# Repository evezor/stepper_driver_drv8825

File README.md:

# DRV8825 Stepper Motor Driver V1.0

*please note this board has been deprecated.

This board uses the Evezor Stamp STMF405 MCU

source: https://github.com/evezor/Evezor-Stamp-STMF405

An edge board with a DRV8825 stepper motor driver, limit switch connections and encoder inputs 

source files: https://github.com/evezor/v0_stepper_driver_drv8825

Evezor® and all associated marks, logos, and designs are registered trademarks and protected by copyright. Unauthorized use or reproduction of these trademarks and copyrighted materials is strictly prohibited.

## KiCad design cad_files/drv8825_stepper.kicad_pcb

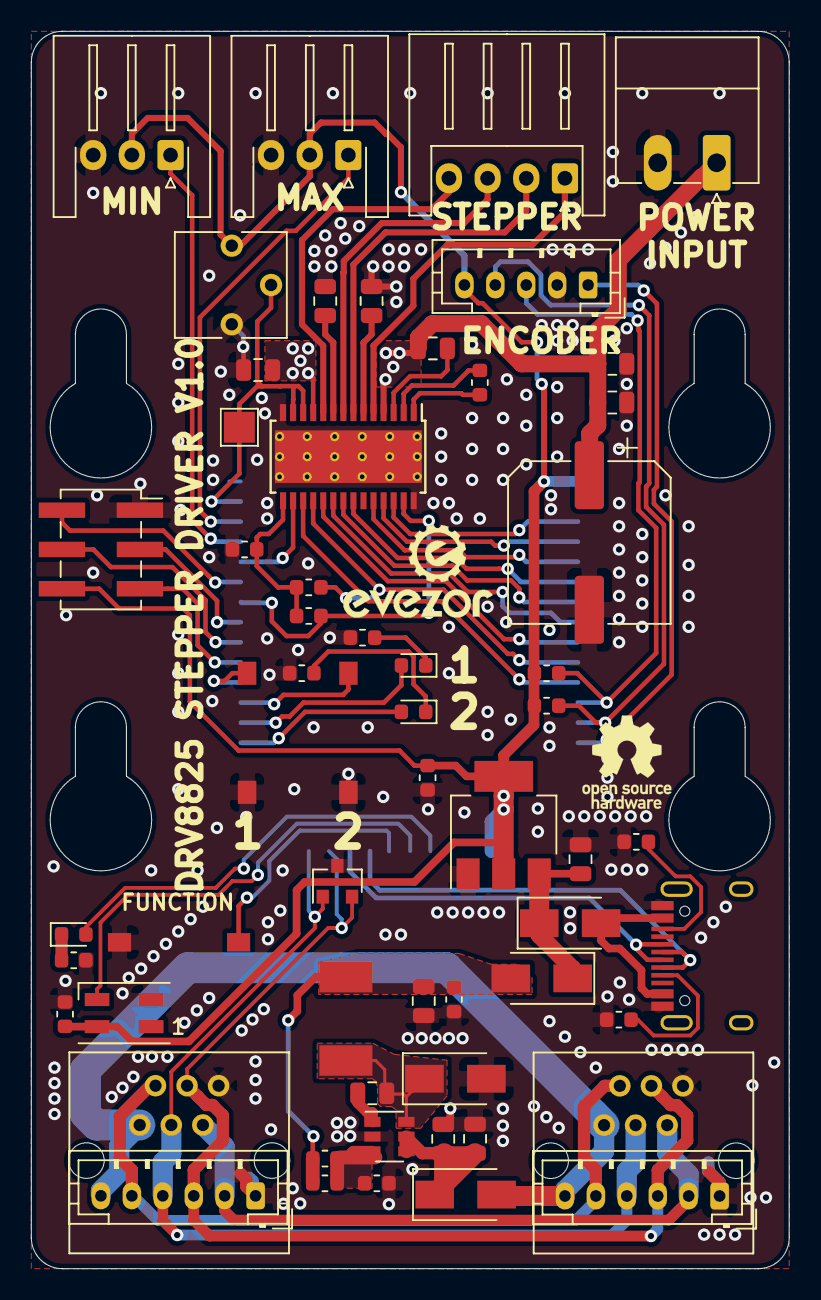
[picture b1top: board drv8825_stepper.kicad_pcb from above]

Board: 2 copper layers, 49.0 x 80.0 mm, 59 parts (1 on the bottom side), 60 nets.

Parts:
C1, C3, C12, C13, C15: .1uF 100V; C_0805_2012Metric
C2, C5, C9, C10: .1uF; C_0603_1608Metric
C4, C7: 4.7uF; C_0805_2012Metric
C6: 22uF; C_0805_2012Metric
C8: 10uF; C_0805_2012Metric
C11: 10 nF; C_0603_1608Metric
C14: 0.47uF; C_0603_1608Metric
C16: 100uF; CP_Elec_10x7.7
D1, D2, D4, D5: SX35_SCHOTTKY; D_SMA
D3, D8, D9: LED; LED_0603_1608Metric
D6: SK6812MINI; LED_SK6812MINI_PLCC4_3.5x3.5mm_P1.75mm
D7: D_TVS_x2_AAC; SOT-23
J1: USB_C_Receptacle_USB2.0; USB_C_Receptacle_HRO_TYPE-C-31-M-12
J2, J3: RJ11; RJ11_C189747_Horizontal
J4, J5: PH; JST_PH_B6B-PH-K_1x06_P2.00mm_Vertical
J6: Conn_02x03_Odd_Even; PinSocket_2x03_P2.54mm_Vertical_SMD
J7: Conn_01x04; JST_XH_S4B-XH-A_1x04_P2.50mm_Horizontal
J9: Conn_01x05; JST_PH_B5B-PH-K_1x05_P2.00mm_Vertical
J10, J11: Conn_01x03; JST_XH_S3B-XH-A-1_1x03_P2.50mm_Horizontal
J12: Conn_01x02; PhoenixContact_MC_1,5_2-G-3.81_1x02_P3.81mm_Horizontal
L1: 22uH; INDUCTOR_7.5X6.6_GCDA0630-220MC
R1: 10k; R_0603_1608Metric
R2: 82k; R_0603_1608Metric
R3, R4: 5.1k; R_0603_1608Metric
R5, R12, R13: 15k; R_0603_1608Metric
R6, R7: 1.5k; R_0603_1608Metric
R8, R9: 0.1; R_0805_2012Metric
R10, R11: 4.7k; R_0603_1608Metric
RV1: R_POT; Potentiometer_Vishay_T73YP_Vertical
SW1, SW2, SW3: SW_Push; SWITCH_2x3_SMD_TACTILE_GREEN
TP1: MCTP; TestPoint_Pad_2.0x2.0mm
U1: SY8401ABC; SOT-23-6
U2: AMS1117-3.3; SOT-223-3_TabPin2
U3: EDGE_STM32F405_CPU_V1; EDGE_STAMP
U4: DRV8825_STEPPER_DRIVER; HTSSOP-28-1EP_4.4x9.7mm_P0.65mm_EP3.4x9.5mm_ThermalVias

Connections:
+3V3: C9.2, C10.1, D6.4, J6.6, J9.5, J10.2, J11.2, R10.2, R11.2, RV1.3, U2.2, U3.1, U3.18
/BOOT: J6.3, U3.36
/BUTTON_1: SW2.1, U3.33
/BUTTON_2: SW3.1, U3.32
/CAN_H: D7.2, J2.3, J3.3, J4.3, J5.3, U3.26
/CAN_L: D7.1, J2.4, J3.4, J4.4, J5.4, U3.27
/CC1: J1.A5, R4.1
/CC2: J1.B5, R3.1
/CURRENT_REF: RV1.2, TP1.1, U3.42, U4.12, U4.13
/D+: J1.A6, J1.B6, U3.25
/D-: J1.A7, J1.B7, U3.24
/DECAY: U3.9, U4.19
/DIR: U3.8, U4.20
/ENABLE: U3.7, U4.21
/ENCDR_NEO: J9.1, U3.14
/FAULT: R6.2, U3.10, U4.18
/FD_H: J2.2, J3.2, J4.2, J5.2
/FD_L: J2.5, J3.5, J4.5, J5.5
/FUNCTION_BUTTON: SW1.1, U3.23
/HBT_LED: D3.2, U3.21
/HOME: R7.2, U3.37, U4.27
/LED_1: D8.2, U3.31
/LED_2: D9.2, U3.30
/M0: U3.5, U4.24
/M1: U3.4, U4.25
/M2: U3.3, U4.26
/MAX: J11.1, U3.41
/MIN: J10.1, U3.40
/NEO_STATUS: D6.3, U3.22
/OLED_SCL: J6.5, U3.34
/OLED_SDA: J6.4, U3.35
/RESET: J6.2, U3.38
/SCL: J9.3, R11.1, U3.12
/SDA: J9.4, R10.1, U3.13
/SLEEP: U3.11, U4.17
/STEP: U3.6, U4.22
/S_RESET: U3.39, U4.16
/USB_VCC: D4.2, J1.A4, J1.A9, J1.B4, J1.B9
/V3P3: C14.1, R6.1, R7.1, U4.15
/VREG_OUT: C2.1, C5.1, C6.1, D5.2, L1.2, R2.1
/V_MOTOR: C7.1, C12.2, C13.2, C15.1, C16.1, J12.1, U4.4, U4.11
GND: C3.2, C4.2, C5.2, C6.2, C7.2, C8.2, C9.1, C10.2, C12.1, C13.1, C14.2, C16.2, D1.2, D6.2, D7.3, J1.A1, J1.A12, J1.B1, J1.B12, J2.1, J3.1, J4.1, J5.1, J6.1, J9.2, J10.3, J11.3, J12.2, R1.1, R3.2, R4.2, R5.1, R8.2, R9.2, R12.1, R13.1, RV1.1, SW1.2, SW2.2, SW3.2, U1.2, U2.1, U3.2, U3.17, U3.43, U4.14, U4.28, U4.29
unnamed: C1.1, D1.1, L1.1, U1.6
unnamed: C1.2, U1.1
unnamed: C2.2, R1.2, R2.2, U1.3
unnamed: C3.1, C4.1, D2.1, U1.4, U1.5
unnamed: C8.1, D4.1, D5.1, U2.3
unnamed: C11.1, U4.2
unnamed: C11.2, U4.1
unnamed: C15.2, U4.3
unnamed: D3.1, R5.2
unnamed: D8.1, R12.2
unnamed: D9.1, R13.2
unnamed: J7.1, U4.5
unnamed: J7.2, U4.7
unnamed: J7.3, U4.8
unnamed: J7.4, U4.10
unnamed: R8.1, U4.9
unnamed: R9.1, U4.6
VBUS: D2.2, J2.6, J3.6, J4.6, J5.6

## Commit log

2021-02-20 add testcode and readme
2021-02-20 update cad
2021-02-20 add datasheet
2021-04-04 add soft limits
2023-09-11 Create LICENSE
2023-09-11 add pics
